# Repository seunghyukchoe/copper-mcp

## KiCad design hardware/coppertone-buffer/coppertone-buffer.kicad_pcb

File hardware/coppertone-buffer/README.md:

# CopperTone Stereo Line Buffer

> **Engineering preview — not approved for fabrication or sale.** This is a
> board-first KiCad 10 artifact intended to exercise CopperMCP's inspection and
> validation workflow. It has no source schematic, ERC, PCB/schematic parity
> proof, simulation, assembled prototype, or measured audio data yet.

CopperTone is a compact, 9 V, two-channel line-level audio buffer built around
the OPA1656 dual JFET-input op amp. The input channels are AC-coupled and biased
to a filtered mid-supply reference; each amplifier is wired at unity gain. The
outputs add 47 ohm isolation, AC coupling, and 100 kohm discharge resistors.

This is deliberately a **line buffer**, not a headphone amplifier. Do not
connect speakers, low-impedance headphones, phantom power, mains, automotive
power, or any safety-critical load.

## Snapshot

| Item | Preview value |
| --- | --- |
| Board | 52 mm × 30 mm, 2-layer FR-4, 1.6 mm |
| Supply | 9 V DC only, J3 pin 1 = `9V_RAW`, pin 2 = `GND` |
| Active device | TI OPA1656IDR, SOIC-8 |
| Audio I/O | 3.5 mm stereo TRS, J1 input and J2 output |
| Signal gain | 1 V/V nominal per channel |
| Input high-pass estimate | 3.4 Hz from 470 nF and 100 kohm, before source effects |
| Output high-pass estimate | load-dependent; about 1.6 Hz into 10 kohm |
| Layout | Ground pours on both layers; no high-impedance input vias |
| KiCad DRC | 0 violations, 0 unconnected items with KiCad 10.0.5 |
| Electrical validation | Not performed |

The estimates above are first-order calculations, not specifications or
measurements. See [`constraints.yaml`](constraints.yaml) and
[`validation/README.md`](validation/README.md) for the exact validation gates.

## Verify the checked-in snapshot

Install KiCad 10 and Python 3.11 or newer, then run:

```sh
./validate.sh
```

Set `KICAD_CLI=/absolute/path/to/kicad-cli` if the CLI is not on `PATH`. The
default command is read-only with respect to this directory. It verifies every
checked-in SHA-256 digest, rebuilds the board in a temporary directory using
stable semantic UUIDs, refills zones, fails on any DRC warning or error, and
compares the regenerated board, project, metrics, DRC, and statistics with the
snapshot while ignoring only KiCad's report timestamp.

To intentionally refresh the public release artifacts, run:

```sh
./validate.sh --refresh-artifacts
```

That explicit maintenance mode updates:

- DRC JSON and board statistics under `validation/`;
- Gerber and Excellon files under `manufacturing/`;
- top/bottom PNG and copper SVG under `media/`;
- a STEP assembly under `mechanical/`; and
- SHA-256 hashes in `validation/SHA256SUMS`.

`generate_board.py` is the preferred editable source for this preview. The
checked-in `.kicad_pcb` is its generated, zone-filled result. Semantic UUIDv5
identities keep the native board serialization stable across identical refreshes.
Other KiCad exports include volatile creation metadata, so refresh their recorded
hashes only when intentionally publishing a new evidence snapshot.

## Circuit walk-through

1. J3 accepts a 9 V DC source. D1 provides series reverse-polarity protection.
2. R1/R2 create `VREF`; C5/C6 filter the virtual ground.
3. J1 tip/ring pass through C1/C2; R3/R4 bias both op-amp inputs to `VREF`.
4. U1A/U1B are unity-gain followers.
5. R5/R6 isolate capacitive cables; C3/C4 block DC; R7/R8 reference J2 to ground.
6. C7 is local U1 supply bypass; C8 is supply bulk decoupling.

## Required work before ordering boards

- Capture and independently review a source schematic.
- Run ERC and KiCad `--schematic-parity`; reconcile every pin and net.
- Verify every custom footprint against the latest manufacturer drawing,
  especially J1/J2 and electrolytic polarity/orientation.
- Confirm component lifecycle, stock, and orderable suffixes in `BOM.csv`.
- Review creepage, clearances, enclosure, ESD, cable-grounding, and power input.
- Assemble at least two prototypes and record DC offsets, current, noise,
  frequency response, crosstalk, clipping margin, load stability, and thermals.
- Obtain an independent fabrication review and explicitly change
  `approved_for_fabrication` only after all gates pass.

## CopperMCP boundary

The geometry is manually authored in the deterministic Python generator.
CopperMCP did **not** autoroute or apply copper to this board. The preview is a
real artifact for testing CopperMCP's current inspect/hash/count and bounded
candidate-validation path while the router and explicit apply operation remain
future work. AI output must never bypass KiCad checks or human authorization.

## Licensing

The source in this directory is licensed under
[`CERN-OHL-S-2.0`](LICENSE). Referenced KiCad 3D models are not copied into this
directory and remain under the KiCad library terms described in
[`PROVENANCE.md`](PROVENANCE.md). There is no CERN endorsement.

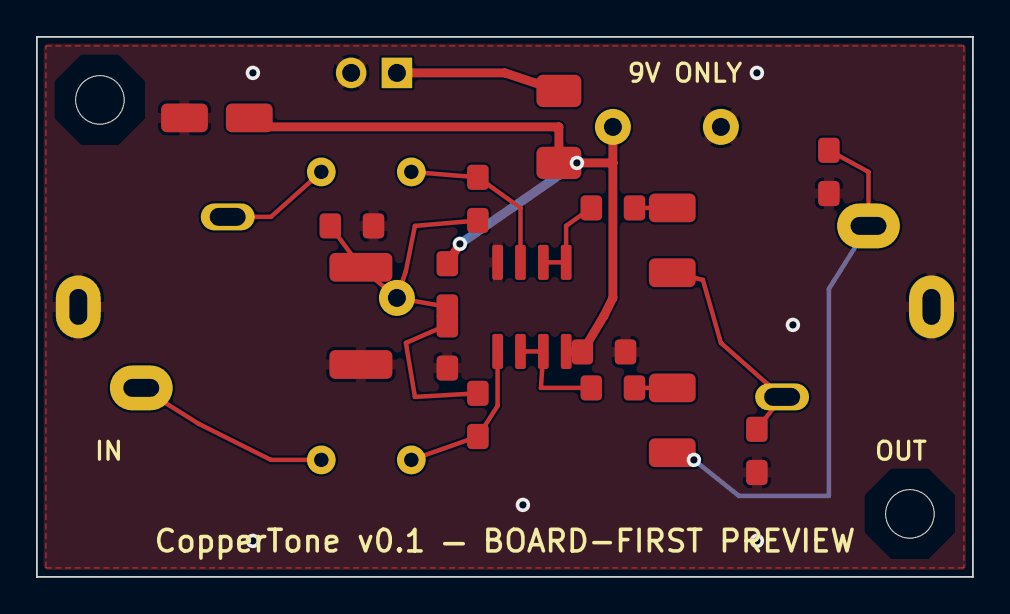
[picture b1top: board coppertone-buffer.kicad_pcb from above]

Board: 2 copper layers, 52.0 x 30.0 mm, 26 parts (0 on the bottom side), 14 nets.

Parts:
C1, C2: 470nF PET film; CopperTone_MKS2_470n_P5.00
C3, C4, C8: 10uF 25V; CopperTone_CP_Elec_4x5.8
C5: 47uF 25V; CopperTone_CP_Elec_6.3x5.8
C6, C7: 100nF X7R; CopperTone_C_0805
D1: SS14; CopperTone_D_SMA
H1, H2: M2.5; CopperTone_MountingHole_2.7mm_M2.5
J1, J2: SJ1-3513N stereo TRS; CopperTone_SJ1-3513N
J3: 9V POWER; CopperTone_PinHeader_1x02_P2.54mm
R1, R2: 47k 1%; CopperTone_R_0805
R3, R4, R7, R8: 100k 1%; CopperTone_R_0805
R5, R6: 47R 1%; CopperTone_R_0805
TP1: VCC; CopperTone_TestPoint_Plated_Hole_D2.0
TP2: VREF; CopperTone_TestPoint_Plated_Hole_D2.0
TP3: GND; CopperTone_TestPoint_Plated_Hole_D2.0
U1: OPA1656IDR; CopperTone_SOIC-8_3.9x4.9mm_P1.27mm

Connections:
9V_RAW: D1.2, J3.1
GND: C5.2, C6.2, C7.2, C8.2, J1.S, J2.S, J3.2, R2.2, R7.2, R8.2, TP3.1, U1.4
L_BUF: R6.1, U1.6, U1.7
L_IN_BIASED: C1.2, R4.2, U1.5
L_IN_RAW: C1.1, J1.T
L_ISO: C3.1, R6.2
L_OUT: C3.2, J2.T, R8.1
R_BUF: R5.1, U1.1, U1.2
R_IN_BIASED: C2.2, R3.1, U1.3
R_IN_RAW: C2.1, J1.R
R_ISO: C4.1, R5.2
R_OUT: C4.2, J2.R, R7.1
VCC: C7.1, C8.1, D1.1, R1.1, TP1.1, U1.8
VREF: C5.1, C6.1, R1.2, R2.1, R3.2, R4.1, TP2.1

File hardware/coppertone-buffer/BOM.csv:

Item,References,Qty,Value,Package_or_footprint,Manufacturer,Preferred_MPN,Sourcing_status,Notes
1,PCB1,1,CopperTone v0.1,52x30mm 2-layer FR-4,Any qualified PCB fab,TBD,HOLD,"Preview outputs only; do not fabricate before validation gates pass"
2,U1,1,OPA1656,SOIC-8 3.9x4.9mm P1.27mm,Texas Instruments,OPA1656IDR,VERIFY,"4.5-36V dual JFET-input op amp; verify pin-1 orientation"
3,"J1 J2",2,3.5mm stereo TRS,SJ1-3513N horizontal THT,Same Sky,SJ1-3513N,VERIFY,"Custom footprint is not mechanically qualified"
4,J3,1,9V power,1x02 P2.54mm vertical THT,Samtec,TSW-102-07-G-S,VERIFY,"Pin 1 = 9V_RAW; pin 2 = GND; add keyed harness if productized"
5,D1,1,SS14,SMA,Diodes Incorporated,SS14-13-F,VERIFY,"Series reverse-polarity protection; stripe/polarity review required"
6,"C1 C2",2,470nF 63V 10% PET film,THT P5.00mm 7.2x3.5mm,WIMA,MKS2C034701C00xxxx,QUALIFY,"Order suffix and lifecycle must be selected; KSSD suffix has lifecycle concerns"
7,"C3 C4 C8",3,10uF 25V,SMD aluminum electrolytic 4x5.8mm,Panasonic,EEEFK1E100R,VERIFY,"Confirm polarity and land pattern against current datasheet"
8,C5,1,47uF 25V,SMD aluminum electrolytic 6.3x5.8mm,Panasonic,EEEFK1E470P,VERIFY,"VREF reservoir; confirm polarity and land pattern"
9,"C6 C7",2,100nF 50V X7R,0805 metric 2012,Murata,GRM21BR71H104KA01L,VERIFY,"Local high-frequency decoupling"
10,"R1 R2",2,47k 1%,0805 metric 2012,Yageo,RC0805FR-0747KL,VERIFY,"VREF divider"
11,"R3 R4 R7 R8",4,100k 1%,0805 metric 2012,Yageo,RC0805FR-07100KL,VERIFY,"Input bias and output discharge"
12,"R5 R6",2,47R 1%,0805 metric 2012,Yageo,RC0805FR-0747RL,VERIFY,"Output isolation"
13,"TP1 TP2 TP3",3,Plated test point,2.0mm plated hole,Unspecified,TBD,DNI,"VCC VREF and GND access; choose hardware after mechanical review"
14,"H1 H2",2,M2.5 mounting hole,2.7mm NPTH,Unspecified,TBD,MECHANICAL,"Fasteners and keepout stack require enclosure review"
